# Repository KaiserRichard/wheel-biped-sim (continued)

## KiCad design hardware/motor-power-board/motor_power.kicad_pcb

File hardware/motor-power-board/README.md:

# Motor power board — rev 2 design study

**Tóm tắt [FROM FILE].** Đây là nghiên cứu thiết kế, chưa chế tạo. Sơ đồ rev 2 fix 4 có ERC 0 lỗi / 0 cảnh báo. Chưa được phát hành để sản xuất: cần đối chiếu footprint relay với bản vẽ khoan chính thức và xác nhận định mức Q1/D11 cho HW3.

[FROM FILE: supplied rev 2 fix 4 ERC] **Design study only; not fabricated.** The current [ERC report](checks/ERC.rpt) reports **0 errors and 0 warnings**. This is schematic consistency evidence, not a safety certification.

- [KiCad project](motor_power.kicad_pro), [root schematic](motor_power.kicad_sch), [PCB](motor_power.kicad_pcb) and [schematic PDF](schematic.pdf).
- [BOM](bom.csv), [symbols](motor_power_symbols.kicad_sym), [footprints](MotorPower.pretty/), and project-relative symbol/footprint tables.
- [Inherited ERC](checks/ERC-inherited.rpt), [inherited DRC](checks/DRC.rpt), [rating rows](S13_rating_rows.csv), [precharge sweep](precharge_sweep.csv) and [pinout comparison](pinout_diff.csv).

## Open pre-fabrication gates

[FROM FILE: supplied rev 2 review/fix notes] Verify the Elesta relay footprint pad positions and pin ordering against the official drilling drawing; the library still carries an unverified marker. Qualify Q1/D11 pulse, transient and thermal ratings against HW3 conditions. Synchronize the PCB, BOM, exported PDF and renders to the approved schematic, then rerun ERC/DRC before manufacturing. The supplied DRC is dated 22 November and the renders show `REV 0.1`; they are inherited layout illustrations, not rev 2 fabrication approval.

## Figures

[FROM FILE] Supplied illustrations, with white backgrounds; no mesh files are distributed:

## Design scripts

[FROM FILE] `design.py`, `circuit.py` and `board.py` are inherited generation scripts requiring KiCad 9 libraries/Python. They predate the manual rev 2 fixes: running them can overwrite those fixes. Keep an independent copy before regenerating. `design_checks.py` repeats the reduced precharge/rating analysis from external S13 input CSVs; point it at an explicit data directory with `--s13-dir`. Those full input sweeps are not included; the exported rating rows and precharge sweep are included. A missing input is an error, never a validation pass.

## What this teaches

[STANDARD PRACTICE] ERC checks electrical declarations; DRC checks layout constraints. Neither establishes component pulse capability or safe stopping. Capacitor charging follows C dV/dt = (Vpack − V)/R − Iload − V/Rbleed; standby load and resistance tolerance change whether the link reaches its gate before the timer ends.

## What the real robot must confirm

[UNKNOWN] Actual drive limits, regenerative pulses, clamp temperature, stop-chain timing, contactor feedback, standby load and relay mounting remain to be measured. The [sim-to-real checklist](../../docs/sim-to-real/sim-to-real-checklist.md) records the proposed measurements.

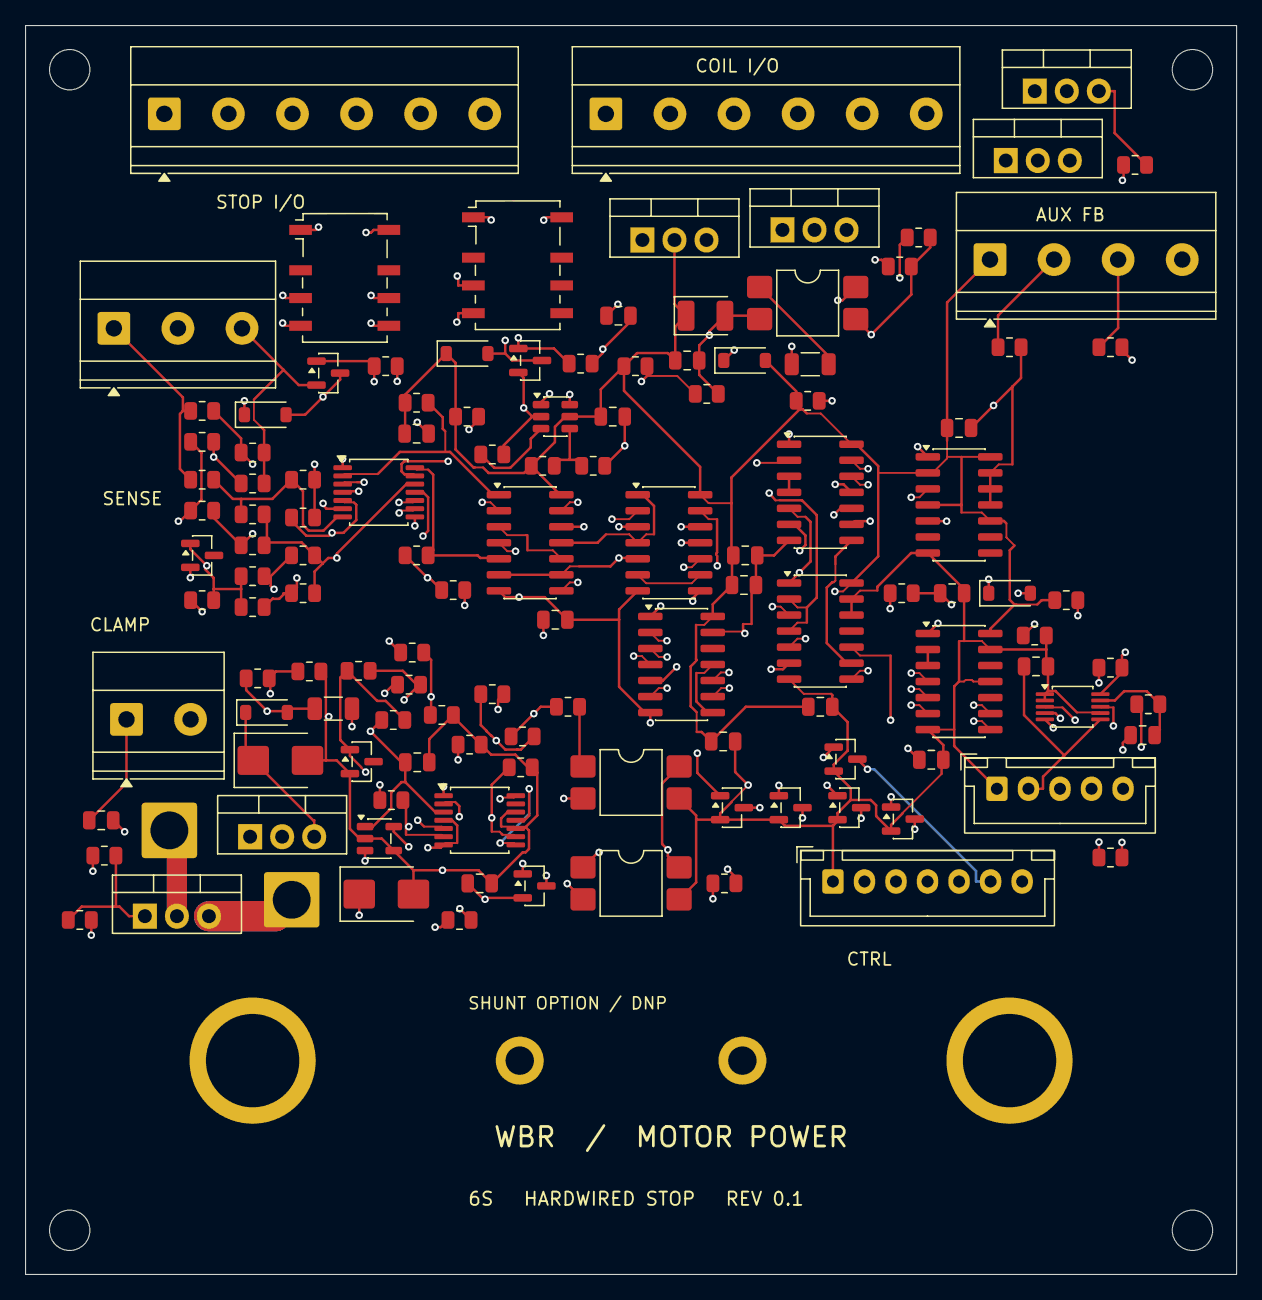
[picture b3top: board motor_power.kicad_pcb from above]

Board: 4 copper layers, 96.0 x 99.0 mm, 129 parts (0 on the bottom side), 97 nets.

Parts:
C1, C3, C4, C5, C7, C8, C9, C10, C11, C12, C13, C16, C17: 100 nF / 50 V; C_0805_2012Metric
C2: 22 µF / 16 V; CP_EIA-3528-21_Kemet-B
C6: 220 nF; C_0805_2012Metric
C14: 100 nF / 100 V; C_0805_2012Metric
C15: 2.2 µF / 25 V; C_1206_3216Metric
C18, C19: 100 nF; C_0805_2012Metric
D4, D5, D7, D8, D12: 1N4148W; D_SOD-123
D6, D10: LM4040A25IDBZR; SOT-23
D9: SMBJ28A; D_SMB
D11: SMBJ48A; D_SMB
H1, H2, H3, H4: M3 mounting; MountingHole_3.2mm_M3
J1: SAFETY CONTACTS; TerminalBlock_Phoenix_MKDS-1,5-6-5.08_1x06_P5.08mm_Horizont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
J2: COIL CONTROL; TerminalBlock_Phoenix_MKDS-1,5-6-5.08_1x06_P5.08mm_Horizont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
J3: AUX NO FEEDBACK; TerminalBlock_Phoenix_MKDS-1,5-4-5.08_1x04_P5.08mm_Horizont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
J4: KELVIN VOLTAGE TAPS; TerminalBlock_Phoenix_MKDS-1,5-3-5.08_1x03_P5.08mm_Horizont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
J5: CLAMP POWER / KELVIN -; TerminalBlock_Phoenix_MKDS-1,5-2-5.08_1x02_P5.08mm_Horizont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
J6: DUMP SW / R3 low; SolderWire-2.5sqmm_1x01_D2.4mm_OD4.4mm
J7: DUMP POWER RETURN; SolderWire-2.5sqmm_1x01_D2.4mm_OD4.4mm
J8: CTRL STATUS / PERMIT; JST_XH_B7B-XH-A_1x07_P2.50mm_Vertical
J9: DNP MONITOR I2C; JST_XH_B5B-XH-A_1x05_P2.50mm_Vertical
K4, K5: G6K-2F-Y DC5; Relay_DPDT_Omron_G6K-2F-Y
Q1: IPP023N10N5; TO-220-3_Vertical
Q2: BSS84; SOT-23
Q4, Q5, Q9, Q10, Q11, Q12, Q13: 2N7002; SOT-23
Q6, Q7, Q8: IRL540NPBF; TO-220-3_Vertical
R24, R25, R26, R27, R28: 47k; R_0805_2012Metric
R29, R41, R43, R63, R64, R79: 10k; R_0805_2012Metric
R30, R31: 680 Ω; R_0805_2012Metric
R32: 5.6k / 0.25 W; R_1206_3216Metric
R40, R42, R44, R47, R62, R70, R73, R75: 100k; R_0805_2012Metric
R45, R48: 10.35k; R_0805_2012Metric
R46, R49: 294k; R_0805_2012Metric
R50, R53: 10.0k; R_0805_2012Metric
R51: 10.2k; R_0805_2012Metric
R52: 45.3k; R_0805_2012Metric
R54: 2.49k; R_0805_2012Metric
R55, R56, R57, R58: 4.7k; R_0805_2012Metric
R59: 113k / 0.1%; R_0805_2012Metric
R60: 1.00M; R_0805_2012Metric
R61: 681k; R_0805_2012Metric
R65, R85: 100 Ω; R_0805_2012Metric
R66: 715 Ω; R_0805_2012Metric
R67: 6.8k; R_0805_2012Metric
R68: 1.00k; R_0805_2012Metric
R69: 10.7k; R_0805_2012Metric
R71: 9.49k; R_0805_2012Metric
R72: 2.05M; R_0805_2012Metric
R74: 8.91k; R_0805_2012Metric
R76: 24.9k; R_0805_2012Metric
R77, R80, R81: 2.2k; R_0805_2012Metric
R78, R82, R83: 10 Ω; R_0805_2012Metric
R84: 4.7 Ω; R_0805_2012Metric
R86: 316 Ω / 0.1%; R_0805_2012Metric
RS1: WSBS8518L5000JT35; WSBS8518_Kelvin
U1, U12: LM317HVT/NOPB; TO-220-3_Vertical
U2, U15, U16: LTV-817S-TA1-C; SMDIP-4_W7.62mm
U3, U13: TLV1704IPWR; TSSOP-14_4.4x5mm_P0.65mm
U4: LTC6993CS6-2#TRMPBF; SOT-23-6
U5, U6, U7: SN74HCS08D; SOIC-14_3.9x8.7mm_P1.27mm
U8: SN74HCS32D; SOIC-14_3.9x8.7mm_P1.27mm
U9, U11: SN74HCT14D; SOIC-14_3.9x8.7mm_P1.27mm
U10: SN74HC74D; SOIC-14_3.9x8.7mm_P1.27mm
U14: UCC27517DBVR; SOT-23-5
U17: INA228AIDGSR; VSSOP-10_3x3mm_P0.5mm

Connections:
+5_CTL: C2.1, C3.1, C4.1, C5.1, C7.1, C8.1, C9.1, C10.1, C11.1, C12.1, C13.1, D4.1, D5.1, D12.2, J3.1, K4.1, K5.1, R29.1, R54.1, R55.1, R56.1, R57.1, R58.1, R60.1, R64.1, R85.1, U1.2, U3.3, U4.5, U5.14, U6.14, U7.14, U8.14, U9.14, U10.2, U10.4, U10.10, U10.14, U11.14
+10_CL: C15.1, C16.1, C17.1, D8.2, Q2.2, R65.1, R67.1, R77.1, R80.1, U12.2, U13.3, U14.1
CLAMP_FAULT: Q12.1, U8.10, U11.8
CLAMP_FAULT_N: J8.6, Q12.3
CLAMP_FEED: C14.1, D8.1, D9.1, J5.1, U12.3
CLAMP_GND: C14.2, C15.2, C16.2, C17.2, D9.2, D10.2, D11.2, J7.1, Q1.3, R66.2, R71.2, R74.2, R76.2, R79.2, U13.10, U13.12, U14.2, U14.4
CLAMP_OPT_N: R64.2, U11.9, U15.4, U16.4
CL_ADJ: R65.2, R66.1, U12.1
CL_NEG: R68.2, R69.2, U13.4, U13.7
CL_ON: Q2.1, R72.1, R77.2, U13.2, U14.3
CL_POS: R70.2, R71.1, R72.2, U13.5
CL_REF: D10.1, R67.2, R68.1, U13.8, U13.11
COIL1_RET: J2.5, Q7.2
COIL2_RET: J2.4, Q6.2
COILP_24: J2.3, R32.1
COILP_RET: J2.6, Q8.2
CONT_EN: Q2.3, R81.1
CONT_LED: R81.2, U16.1
CONT_OPTO_K: U13.14, U16.2
CTL_ADJ: R85.2, R86.1, U1.1
DELTA_OK: U5.3, U5.10
DRAIN_S: R75.2, R76.1, U13.9
DUMP_GATE: Q1.1, R78.2, R79.1
DUMP_GATE_RAW: R78.1, U14.5
DUMP_SW: D11.1, J6.1, Q1.2, R75.1
DV_FWD: R55.2, U3.2, U5.1
DV_REV: R56.2, U3.1, U5.2
EDM_1: J1.2, K4.4
EDM_4: J1.5, K5.3
ESTOP_OK_N: J8.7, Q13.3
FAULT_DELAY: C6.1, D7.2, R62.2, U9.9
FAULT_DELAY_N: U9.8, U9.11
FAULT_LOCAL: U9.10, U11.5
FAULT_N: U7.13, U11.6
FAULT_RAW: U7.8, U8.9
GND: C1.2, C2.2, C3.2, C4.2, C5.2, C6.2, C7.2, C8.2, C9.2, C10.2, C11.2, C12.2, C13.2, C19.2, D6.2, J2.2, J3.4, J4.3, J8.1, J9.1, Q4.2, Q5.2, Q6.3, Q7.3, Q8.3, Q9.2, Q10.2, Q11.2, Q12.2, Q13.2, R24.2, R25.2, R26.2, R27.2, R28.2, R30.2, R31.2, R41.2, R43.2, R45.2, R48.2, R51.2, R53.2, R59.2, R61.2, R63.2, R86.2, U2.2, U2.3, U3.12, U4.2, U5.7, U6.7, U7.7, U8.7, U8.12, U8.13, U9.7, U9.13, U10.7, U10.11, U10.12, U10.13, U11.7, U11.11, U11.13, U15.3, U16.3, U17.1, U17.2, U17.7
INA_ALERT: J9.5, U17.3
INA_N: C18.2, R83.2, U17.9
INA_P: C18.1, R82.2, U17.10
INA_SCL: J9.4, U17.5
INA_SDA: J9.3, U17.4
INA_VBUS: R84.2, U17.8
IS_N: R83.1, R84.1, RS1.4
IS_P: R82.1, RS1.3
K1_FB: J3.2, Q9.1, R30.1, U7.1, U9.3
K1_FB_N: J8.3, Q9.3
K1_NOT: U6.10, U9.4
K2_CMD: Q6.1, R26.1, U6.11
K2_FB: J3.3, Q10.1, R31.1, U5.4
K2_FB_N: J8.4, Q10.3
K2_HOLD: U6.13, U8.3
K2_PROVED: U5.6, U5.9, U6.5, U7.2
K4_COIL: D4.2, K4.8, Q4.3
K5_COIL: D5.2, K5.8, Q5.3
KPRE_CMD: Q8.1, R28.1, U6.8
KP_READY: U6.6, U6.9
LINK_B: R47.2, R48.1, R49.1, U3.5
LINK_GOOD: Q11.1, U7.6, U8.5
LINK_GOOD_N: J8.5, Q11.3
LINK_KMIN: J5.2, R69.1
LINK_LOW: Q5.1, R25.1, R58.2, U3.13
LINK_S: R42.2, R43.1, U3.6, U3.10
LINK_SENSE: J4.2, R42.1, R47.1, R70.1, R73.1
LOW_REF: R52.2, R53.1, U3.11
MAINS_FB: U7.3, U7.4
MID_B: R44.2, R45.1, R46.1, U3.7
MID_HIGH: R57.2, U3.14, U5.5
MID_REF: R50.2, R51.1, U3.8
MID_S: R40.2, R41.1, U3.4, U3.9
OV_LED: R80.2, U15.1
OV_OPTO_K: U13.1, U15.2
OV_S: R73.2, R74.1, U13.6
PERMIT_IN: J8.2, R63.1, U11.1
PERMIT_N: U11.2, U11.3
PERMIT_RELAY: Q4.1, R24.1, U7.11
PRE_IN: J4.1, R40.1, R44.1
PRE_WINDOW: U5.11, U6.1, U6.4
RADIO_B: J1.3, K4.6
READY: U5.8, U6.2
REF2V5: D6.1, R46.2, R49.2, R50.1, R52.1, R54.2
RESET_OUT: J1.6, K5.4
RUN: Q7.1, R27.1, U7.5, U8.1, U10.5
RUN_CLK: U6.3, U10.3
SAFE: Q13.1, U4.1, U5.12, U6.12, U7.9, U9.2, U10.1
SAFE_LED: R32.2, U2.1
SAFE_N: R29.2, U2.4, U9.1
SR_B: J1.4, K4.5
STAGE_OK: U8.6, U9.5
STOP_24: C1.1, D12.1, J2.1, U1.3
T11_3V3: C19.1, J9.2, U17.6
T11_PERMIT: U7.12, U11.4
THERM_A: J1.1, K4.3
TRIP_REQ: D7.1, R62.1, U8.8
T_DIV: R60.2, R61.1, U4.4
T_SET: R59.1, U4.3
UNPROVED: U7.10, U9.6
WINDOW: U4.6, U5.13, U8.2, U8.4

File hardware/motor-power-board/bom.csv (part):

"Reference","Value","Footprint","MPN","Assembly","Notes","Quantity","DNP"
"BT1","6S pack + BMS","","6S pack + BMS","HARNESS","18.0–25.2 V; capacity and fault current TBD","1",""
"C1","100 nF / 50 V","Capacitor_SMD:C_0805_2012Metric","GRM21BR71H104KA01L","PCB","","1",""
"C2","22 µF / 16 V","Capacitor_Tantalum_SMD:CP_EIA-3528-21_Kemet-B","22 µF / 16 V","PCB","Control reservoir at U1 output, check regulator temperature and transient droop","1",""
"C3","100 nF / 50 V","Capacitor_SMD:C_0805_2012Metric","GRM21BR71H104KA01L","PCB","","1",""
"C4","100 nF / 50 V","Capacitor_SMD:C_0805_2012Metric","GRM21BR71H104KA01L","PCB","","1",""
"C5","100 nF / 50 V","Capacitor_SMD:C_0805_2012Metric","GRM21BR71H104KA01L","PCB","","1",""
"C6","220 nF","Capacitor_SMD:C_0805_2012Metric","220 nF","PCB","","1",""
"C7","100 nF / 50 V","Capacitor_SMD:C_0805_2012Metric","GRM21BR71H104KA01L","PCB","","1",""
"C8","100 nF / 50 V","Capacitor_SMD:C_0805_2012Metric","GRM21BR71H104KA01L","PCB","","1",""
"C9","100 nF / 50 V","Capacitor_SMD:C_0805_2012Metric","GRM21BR71H104KA01L","PCB","","1",""
"C10","100 nF / 50 V","Capacitor_SMD:C_0805_2012Metric","GRM21BR71H104KA01L","PCB","","1",""
"C11","100 nF / 50 V","Capacitor_SMD:C_0805_2012Metric","GRM21BR71H104KA01L","PCB","","1",""
"C12","100 nF / 50 V","Capacitor_SMD:C_0805_2012Metric","GRM21BR71H104KA01L","PCB","","1",""
"C13","100 nF / 50 V","Capacitor_SMD:C_0805_2012Metric","GRM21BR71H104KA01L","PCB","","1",""
"C14","100 nF / 100 V","Capacitor_SMD:C_0805_2012Metric","GRM21BR72A104KA01L","PCB","","1",""
"C15","2.2 µF / 25 V","Capacitor_SMD:C_1206_3216Metric","2.2 µF / 25 V","PCB","","1",""
"C16","100 nF / 50 V","Capacitor_SMD:C_0805_2012Metric","GRM21BR71H104KA01L","PCB","","1",""
"C17","100 nF / 50 V","Capacitor_SMD:C_0805_2012Metric","GRM21BR71H104KA01L","PCB","","1",""
"C18","100 nF","Capacitor_SMD:C_0805_2012Metric","100 nF","DNP","","1","DNP"
"C19","100 nF","Capacitor_SMD:C_0805_2012Metric","100 nF","DNP","","1","DNP"
"D4","1N4148W","Diode_SMD:D_SOD-123","1N4148W","PCB","","1",""
"D5","1N4148W","Diode_SMD:D_SOD-123","1N4148W","PCB","","1",""
"D6","LM4040A25IDBZR","Package_TO_SOT_SMD:SOT-23","LM4040A25IDBZR","PCB","2.500 V A-grade shunt reference","1",""
"D7","1N4148W","Diode_SMD:D_SOD-123","1N4148W","PCB","","1",""
"D8","1N4148W","Diode_SMD:D_SOD-123","1N4148W","PCB","","1",""
"D9","SMBJ28A","Diode_SMD:D_SMB","SMBJ28A","PCB","","1",""
"D10","LM4040A25IDBZR","Package_TO_SOT_SMD:SOT-23","LM4040A25IDBZR","PCB","","1",""
"D11","SMBJ48A","Diode_SMD:D_SMB","SMBJ48A","PCB","Validate drain turn-off transient against 100 V rating","1",""
"D12","1N4148W","Diode_SMD:D_SOD-123","1N4148W","PCB","","1",""
"F1","Main fuse TBD","","Main fuse TBD","HARNESS",">=60 V DC holder; first fuse at pack","1",""
"F2","Motor feeder fuse TBD","","Motor feeder fuse TBD","HARNESS",">=60 V DC; coordinated with branch and BMS","1",""
"F3","Logic fuse TBD","","Logic fuse TBD","HARNESS","Independent AUX supply branch","1",""
"F4","Stop supply fuse TBD","","Stop supply fuse TBD","HARNESS","Independently protected supply input","1",""
"F5","Branch fuse TBD","","Branch fuse TBD","HARNESS","≥60 V DC fuse position; allocation TBD","1",""
"F6","Branch fuse TBD","","Branch fuse TBD","HARNESS","≥60 V DC fuse position; allocation TBD","1",""
"F7","Branch fuse TBD","","Branch fuse TBD","HARNESS","≥60 V DC fuse position; allocation TBD","1",""
"F8","Branch fuse TBD","","Branch fuse TBD","HARNESS","≥60 V DC fuse position; allocation TBD","1",""
"F9","Branch fuse TBD","","Branch fuse TBD","HARNESS","≥60 V DC fuse position; allocation TBD","1",""
"F10","Branch fuse TBD","","Branch fuse TBD","HARNESS","≥60 V DC fuse position; allocation TBD","1",""
"F11","Clamp control tap fuse TBD","","Clamp control tap fuse TBD","HARNESS","Rated 60 V DC, independent tap","1",""
"F12","Dump fuse TBD","","Dump fuse TBD","HARNESS","Coordinate healthy pulse, short interruption and thermal latch","1",""
"J1","SAFETY CONTACTS","TerminalBlock_Phoenix:TerminalBlock_Phoenix_MKDS-1,5-6-5.08_1x06_P5.08mm_Horizontal","SAFETY CONTACTS","PCB","Low-current dry contacts. Feed EDM_1 to both S12 and K1 NC.","1",""
"J2","COIL CONTROL","TerminalBlock_Phoenix:TerminalBlock_Phoenix_MKDS-1,5-6-5.08_1x06_P5.08mm_Horizontal","COIL CONTROL","PCB","External coil positives routed directly through safety relay outputs","1",""
"J3","AUX NO FEEDBACK","TerminalBlock_Phoenix:TerminalBlock_Phoenix_MKDS-1,5-4-5.08_1x04_P5.08mm_Horizontal","AUX NO FEEDBACK","PCB","Second auxiliaries; use verified dry-circuit contacts","1",""
"J4","KELVIN VOLTAGE TAPS","TerminalBlock_Phoenix:TerminalBlock_Phoenix_MKDS-1,5-3-5.08_1x03_P5.08mm_Horizontal","KELVIN VOLTAGE TAPS","PCB","Separate sense wires and protected taps; 5.08 mm pitch","1",""
"J5","CLAMP POWER / KELVIN -","TerminalBlock_Phoenix:TerminalBlock_Phoenix_MKDS-1,5-2-5.08_1x02_P5.08mm_Horizontal","CLAMP POWER / KELVIN -","PCB","","1",""
"J6","DUMP SW / R3 low","Connector_Wire:SolderWire-2.5sqmm_1x01_D2.4mm_OD4.4mm","DUMP SW / R3 low","PCB","","1",""
"J7","DUMP POWER RETURN","Connector_Wire:SolderWire-2.5sqmm_1x01_D2.4mm_OD4.4mm","DUMP POWER RETURN","PCB","","1",""
"J8","CTRL STATUS / PERMIT","Connector_JST:JST_XH_B7B-XH-A_1x07_P2.50mm_Vertical","CTRL STATUS / PERMIT","PCB","","1",""
"J9","DNP MONITOR I2C","Connector_JST:JST_XH_B5B-XH-A_1x05_P2.50mm_Vertical","DNP MONITOR I2C","DNP","Separate optional monitor harness, 3.3 V pull-ups at host","1","DNP"
"K1","C310S/150 main","","C310S/150 24I-V2","HARNESS","C310S catalog p. 8 terminal map, external bolted high-current contacts","1",""
"K2","C310S/150 main","","C310S/150 24I-V2","HARNESS","C310S catalog p. 8 terminal map, external bolted high-current contacts","1",""
"K3","C310S/150 precharge","","C310S/150 24I-V1","HARNESS","C310S catalog p. 8 terminal map, external bolted high-current contacts","1",""
"K4","G6K-2F-Y DC5","Relay_SMD:Relay_DPDT_Omron_G6K-2F-Y","G6K-2F-Y DC5","PCB","Dual-pole CTRL permit / timeout inhibiting dry relay","1",""
"K5","G6K-2F-Y DC5","Relay_SMD:Relay_DPDT_Omron_G6K-2F-Y","G6K-2F-Y DC5","PCB","Zero-link permissive in series with independent EDM","1",""
"PS1","PYH200-72WS24 carrier","","TDK-Lambda PYH200-72WS24","HARNESS","External 24 V, 8.4 A nominal; apply vendor input/output carrier circuit","1",""
"Q1","IPP023N10N5","Package_TO_SOT_THT:TO-220-3_Vertical","IPP023N10N5","PCB","100 V, TO-220; mounted at dump wire pads","1",""
"Q2","BSS84","Package_TO_SOT_SMD:SOT-23","BSS84","PCB","","1",""
"Q4","2N7002","Package_TO_SOT_SMD:SOT-23","2N7002","PCB","","1",""
"Q5","2N7002","Package_TO_SOT_SMD:SOT-23","2N7002","PCB","","1",""
"Q6","IRL540NPBF","Package_TO_SOT_THT:TO-220-3_Vertical","IRL540NPBF","PCB","C310S has integrated suppression. External harness to A2, no additional coil suppressor","1",""
"Q7","IRL540NPBF","Package_TO_SOT_THT:TO-220-3_Vertical","IRL540NPBF","PCB","C310S has integrated suppression. External harness to A2, no additional coil suppressor","1",""
"Q8","IRL540NPBF","Package_TO_SOT_THT:TO-220-3_Vertical","IRL540NPBF","PCB","C310S has integrated suppression. External harness to A2, no additional coil suppressor","1",""
"Q9","2N7002","Package_TO_SOT_SMD:SOT-23","2N7002","PCB","","1",""
"Q10","2N7002","Package_TO_SOT_SMD:SOT-23","2N7002","PCB","","1",""
"Q11","2N7002","Package_TO_SOT_SMD:SOT-23","2N7002","PCB","","1",""
"Q12","2N7002","Package_TO_SOT_SMD:SOT-23","2N7002","PCB","","1",""
"Q13","2N7002","Package_TO_SOT_SMD:SOT-23","2N7002","PCB","","1",""
"R1","3.0 Ω / ±5%","","Vishay LPS600 3R0","HARNESS","Heatsink-mounted, ≥150 J / 0.65 s design screen","1",""
"R2","330 Ω / 5 W","","Vishay AC05 330R class","HARNESS","External bleeder near link","1",""
"R3","1.5 Ω / ±10%","","Vishay LPS600 1R5","HARNESS","External heatsink and NC thermal switch","1",""
"R24","47k","Resistor_SMD:R_0805_2012Metric","47k","PCB","","1",""
"R25","47k","Resistor_SMD:R_0805_2012Metric","47k","PCB","","1",""
"R26","47k","Resistor_SMD:R_0805_2012Metric","47k","PCB","","1",""
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
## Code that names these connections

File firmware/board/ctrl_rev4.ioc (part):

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Mcu.Name=STM32H723V(E-G)Tx
Mcu.Package=LQFP100
Mcu.UserName=STM32H723VGTx
board=custom
PD0.Signal=FDCAN1_RX
PD0.GPIO_Label=CAN1_RX
PD0.GPIO_Speed=GPIO_SPEED_FREQ_VERY_HIGH
PD0.GPIO_PuPd=GPIO_NOPULL
PD1.Signal=FDCAN1_TX
PD1.GPIO_Label=CAN1_TX
PD1.GPIO_Speed=GPIO_SPEED_FREQ_VERY_HIGH
PD1.GPIO_PuPd=GPIO_NOPULL
PB5.Signal=FDCAN2_RX
PB5.GPIO_Label=CAN2_RX
PB5.GPIO_Speed=GPIO_SPEED_FREQ_VERY_HIGH
PB5.GPIO_PuPd=GPIO_NOPULL
PB6.Signal=FDCAN2_TX
PB6.GPIO_Label=CAN2_TX
PB6.GPIO_Speed=GPIO_SPEED_FREQ_VERY_HIGH
PB6.GPIO_PuPd=GPIO_NOPULL
PD12.Signal=FDCAN3_RX
PD12.GPIO_Label=CAN3_RX
PD12.GPIO_Speed=GPIO_SPEED_FREQ_VERY_HIGH
PD12.GPIO_PuPd=GPIO_NOPULL
PD13.Signal=FDCAN3_TX
PD13.GPIO_Label=CAN3_TX
PD13.GPIO_Speed=GPIO_SPEED_FREQ_VERY_HIGH
PD13.GPIO_PuPd=GPIO_NOPULL
PC6.Signal=USART6_TX
PC6.GPIO_Label=CRSF_TX_FROM_MCU
PC6.GPIO_Speed=GPIO_SPEED_FREQ_VERY_HIGH
PC6.GPIO_PuPd=GPIO_PULLUP
PC7.Signal=USART6_RX
PC7.GPIO_Label=CRSF_RX_TO_MCU
PC7.GPIO_Speed=GPIO_SPEED_FREQ_VERY_HIGH
PC7.GPIO_PuPd=GPIO_PULLUP
PA9.Signal=GPIO_Input
PA9.GPIO_Label=VBUS_SENSE
PA9.GPIO_Speed=GPIO_SPEED_FREQ_LOW
PA9.GPIO_PuPd=GPIO_NOPULL
PA11.Signal=USB_OTG_HS_DM
PA11.GPIO_Label=USB_D_N
PA11.GPIO_Speed=GPIO_SPEED_FREQ_VERY_HIGH
PA11.GPIO_PuPd=GPIO_NOPULL
PA12.Signal=USB_OTG_HS_DP
PA12.GPIO_Label=USB_D_P
PA12.GPIO_Speed=GPIO_SPEED_FREQ_VERY_HIGH
PA12.GPIO_PuPd=GPIO_NOPULL
PB12.Signal=GPXTI12
PB12.GPIO_Label=WIRED_STOP_OPEN
PB12.GPIO_Speed=GPIO_SPEED_FREQ_HIGH
PB12.GPIO_PuPd=GPIO_NOPULL
PB12.GPIO_ModeDefaultEXTI=GPIO_MODE_IT_RISING
PD7.Signal=GPXTI7
PD7.GPIO_Label=ESTOP_STATUS
PD7.GPIO_Speed=GPIO_SPEED_FREQ_HIGH
PD7.GPIO_PuPd=GPIO_NOPULL
PD7.GPIO_ModeDefaultEXTI=GPIO_MODE_IT_RISING
PD11.Signal=GPIO_Output
PD11.GPIO_Label=MCU_HEARTBEAT
PD11.GPIO_Speed=GPIO_SPEED_FREQ_HIGH
PD11.GPIO_PuPd=GPIO_NOPULL
PD11.PinState=GPIO_PIN_RESET
PE12.Signal=SPI4_SCK
PE12.GPIO_Label=SPI4_SCK_MCU
PE12.GPIO_Speed=GPIO_SPEED_FREQ_HIGH
PE12.GPIO_PuPd=GPIO_NOPULL
PE13.Signal=SPI4_MISO
PE13.GPIO_Label=SPI4_MISO
PE13.GPIO_Speed=GPIO_SPEED_FREQ_HIGH
PE13.GPIO_PuPd=GPIO_NOPULL
PE14.Signal=SPI4_MOSI
PE14.GPIO_Label=SPI4_MOSI_MCU
PE14.GPIO_Speed=GPIO_SPEED_FREQ_HIGH
PE14.GPIO_PuPd=GPIO_NOPULL
PE3.Signal=GPIO_Output
PE3.GPIO_Label=ACC_CS_MCU
PE3.GPIO_Speed=GPIO_SPEED_FREQ_HIGH
PE3.GPIO_PuPd=GPIO_PULLUP
PE3.PinState=GPIO_PIN_SET
PE4.Signal=GPIO_Output
PE4.GPIO_Label=GYRO_CS_MCU
PE4.GPIO_Speed=GPIO_SPEED_FREQ_HIGH
PE4.GPIO_PuPd=GPIO_PULLUP
PE4.PinState=GPIO_PIN_SET
PE10.Signal=GPIO_Input
PE10.GPIO_Label=ACC_INT
PE10.GPIO_Speed=GPIO_SPEED_FREQ_LOW
PE10.GPIO_PuPd=GPIO_NOPULL
PE11.Signal=GPIO_Input
PE11.GPIO_Label=GYRO_INT
PE11.GPIO_Speed=GPIO_SPEED_FREQ_LOW
PE11.GPIO_PuPd=GPIO_NOPULL
PB0.Signal=GPIO_Output
PB0.GPIO_Label=BUZZER
PB0.GPIO_Speed=GPIO_SPEED_FREQ_LOW
PB0.GPIO_PuPd=GPIO_PULLDOWN
PB0.PinState=GPIO_PIN_RESET
PB1.Signal=GPIO_Output
PB1.GPIO_Label=HEAT_PWM
PB1.GPIO_Speed=GPIO_SPEED_FREQ_LOW
PB1.GPIO_PuPd=GPIO_PULLDOWN
PB1.PinState=GPIO_PIN_RESET
PD4.Signal=GPIO_Output
PD4.GPIO_Label=RUN_LED
PD4.GPIO_Speed=GPIO_SPEED_FREQ_LOW
PD4.GPIO_PuPd=GPIO_NOPULL
PD4.PinState=GPIO_PIN_RESET
PD5.Signal=GPIO_Output
PD5.GPIO_Label=FAULT_LED
PD5.GPIO_Speed=GPIO_SPEED_FREQ_LOW
PD5.GPIO_PuPd=GPIO_NOPULL
PD5.PinState=GPIO_PIN_RESET
PH0-OSC_IN.Signal=RCC_OSC_IN
PH0-OSC_IN.GPIO_Label=HSE_IN
PH1-OSC_OUT.Signal=RCC_OSC_OUT
PH1-OSC_OUT.GPIO_Label=HSE_OUT
PA13.Signal=SYS_JTMS-SWDIO
PA13.GPIO_Label=SWDIO
PA14.Signal=SYS_JTCK-SWCLK
PA14.GPIO_Label=SWCLK
RCC.HSE_VALUE=24000000
RCC.HSEState=RCC_HSE_ON
RCC.SYSCLKSource=RCC_SYSCLKSOURCE_PLLCLK
RCC.SYSCLKDivider=RCC_SYSCLK_DIV1
RCC.SYSCLKFreq_VALUE=520000000

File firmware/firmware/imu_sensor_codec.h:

/*
 * FW10 IMU sensor codec (portable, host-tested).
 *
 * The CTRL rev4 IMU sensor (U8) is a two-die part: an accelerometer die and a
 * gyroscope die on one SPI bus (SPI4: PE12 SCK, PE13 MISO, PE14 MOSI) with
 * separate chip selects (PE3 ACC_CS, PE4 GYRO_CS) [FROM FILE ctrl_rev4.net].
 * This module holds the register map, the boot configuration sequence, the SPI
 * frame layout (the accel die returns one dummy byte after the address) and the
 * raw -> SI conversion and sensor -> body axis map. The register values are
 * [ASSUMED] from the sensor family datasheet and must be confirmed in bench
 * stage 2.1 (chip-ID read-back is checked at boot and reported in telemetry).
 *
 * Pure C11, zero HAL dependencies. Simulation/design only.
 */

#ifndef WBR_IMU_SENSOR_CODEC_H
#define WBR_IMU_SENSOR_CODEC_H

#include <stdint.h>

#define IMU_DIE_ACCEL               0u
#define IMU_DIE_GYRO                1u

#define IMU_SPI_READ_FLAG           0x80u

/* Accelerometer die */
#define IMU_ACC_REG_CHIP_ID         0x00u
#define IMU_ACC_CHIP_ID_VALUE       0x1Eu
#define IMU_ACC_REG_ERR             0x02u
#define IMU_ACC_REG_DATA            0x12u  /* X LSB .. Z MSB, 6 bytes */
#define IMU_ACC_REG_TEMP_MSB        0x22u  /* MSB, LSB */
#define IMU_ACC_REG_CONF            0x40u
#define IMU_ACC_REG_RANGE           0x41u
#define IMU_ACC_REG_PWR_CONF        0x7Cu
#define IMU_ACC_REG_PWR_CTRL        0x7Du
#define IMU_ACC_REG_SOFTRESET       0x7Eu
#define IMU_ACC_CONF_VALUE          0xABu  /* normal filter, ODR 800 Hz */
#define IMU_ACC_RANGE_VALUE         0x01u  /* +/-6 g */
#define IMU_ACC_RANGE_G             6.0

/* Gyroscope die */
#define IMU_GYR_REG_CHIP_ID         0x00u
#define IMU_GYR_CHIP_ID_VALUE       0x0Fu
#define IMU_GYR_REG_DATA            0x02u  /* X LSB .. Z MSB, 6 bytes */
#define IMU_GYR_REG_RANGE           0x0Fu
#define IMU_GYR_REG_BANDWIDTH       0x10u
#define IMU_GYR_REG_LPM1            0x11u
#define IMU_GYR_REG_SOFTRESET       0x14u
#define IMU_GYR_RANGE_VALUE         0x00u  /* +/-2000 deg/s */
#define IMU_GYR_BANDWIDTH_VALUE     0x02u  /* ODR 1000 Hz, 116 Hz filter */
#define IMU_GYR_RANGE_DPS           2000.0

#define IMU_SOFTRESET_CMD           0xB6u

#define IMU_STANDARD_GRAVITY        9.80665
#define IMU_INIT_MAX_STEPS          16u

typedef enum {
    IMU_STEP_DUMMY_READ = 0,   /* read CHIP_ID, ignore value (accel SPI-mode switch) */
    IMU_STEP_WRITE      = 1,
    IMU_STEP_CHECK      = 2    /* read reg, (value & mask) must equal expect */
} ImuStepKind;

typedef struct {
    uint8_t  kind;      /* ImuStepKind */
    uint8_t  die;       /* IMU_DIE_ACCEL / IMU_DIE_GYRO */
    uint8_t  reg;
    uint8_t  value;     /* WRITE value or CHECK expected value */
    uint8_t  mask;      /* CHECK mask */
    uint16_t delay_ms;  /* wait after the step */
} ImuInitStep;

/* Sensor-frame -> body-frame axis map: body[i] = sign[i] * sensor[src[i]].
 * Default identity is ASSUMED; bench stage 2.2 (hand tilt) fixes it. */
typedef struct {
    uint8_t src[3];
    int8_t  sign[3];
} ImuAxisMap;

typedef struct {
    double  accel_m_s2[3];
    double  gyro_rad_s[3];
    float   temp_c;
    int16_t accel_raw[3];
    int16_t gyro_raw[3];
} ImuSample;

/* Boot configuration sequence; returns number of steps written to out[]. */
uint32_t imu_codec_init_sequence(ImuInitStep out[IMU_INIT_MAX_STEPS]);

/* Bytes of dummy data between the address byte and the first data byte. */
uint8_t imu_codec_read_dummy_bytes(uint8_t die);

/* Build an SPI read frame: tx[0] = reg | 0x80, rest 0. Returns total length
 * (1 + dummy + n) or 0 if it does not fit in cap. */
uint32_t imu_codec_build_read(uint8_t die, uint8_t reg, uint32_t n, uint8_t *tx, uint32_t cap);

/* Conversions */
double imu_codec_accel_lsb_to_m_s2(int16_t raw);
double imu_codec_gyro_lsb_to_rad_s(int16_t raw);
float  imu_codec_temp_c(uint8_t msb, uint8_t lsb);
int16_t imu_codec_le16(const uint8_t *p);

/* Decode the 6-byte data payloads (after the dummy bytes) into SI + body frame. */
void imu_codec_decode(const ImuAxisMap *map, const uint8_t acc6[6], const uint8_t gyr6[6],
                      uint8_t temp_msb, uint8_t temp_lsb, ImuSample *out);

ImuAxisMap imu_codec_default_axis_map(void);
uint8_t    imu_codec_axis_map_valid(const ImuAxisMap *map);

#endif /* WBR_IMU_SENSOR_CODEC_H */
